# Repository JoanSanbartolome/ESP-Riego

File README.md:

# ESP-Riego

Controlador inalámbrico de riego por goteo basado en ESP32 e integrado en Home Assistant mediante ESPHome.

Este repositorio contiene el rediseño (v2) de la PCB desarrollada en el Trabajo Fin de Grado de Joan San Bartolomé Ferri. El proyecto original del TFG no se modifica: se importa como referencia y la v2 se diseña desde cero a partir de su análisis.

La v2 tiene 6 salidas de 24 V DC con *high-side* inteligente y limitador común, sensor de temperatura y humedad en placa, pulsadores y un conector de expansión por I²C.

## Estado

| Fase | Estado | Etiqueta |
|---|---|---|
| 0. Análisis, especificaciones y plan | ✅ | — |
| 1. Importación de la v1 a KiCad 10 | ✅ | `v1.1-tfg` |
| 2. Arquitectura y componentes | ✅ (falta la alternativa de U1) | — |
| 3. Esquema v2 | ✅ | `v2.0-sch` |
| 4. Layout v2 | ⏳ (prueba de colocación, SPEC-0037) | — |
| 5. Fabricación | — | — |
| 6. Firmware y validación | — | — |

El esquema tiene ERC limpio, 12 páginas y 187 piezas, y cuesta 27,46 USD por placa en un pedido de 5. Lo que toca ahora está en [`gestion/ESTADO.md`](gestion/ESTADO.md).

## Documentación

1. [Análisis de la PCB v1](docs/01-analisis-v1.md): estado de la placa del TFG y hallazgos.
2. [Especificaciones de la PCB v2](docs/02-especificaciones-v2.md): requisitos y criterios de aceptación.
3. [Plan de diseño](docs/03-plan-de-diseno.md): fases e hitos.
4. [Arquitectura](docs/diseno/arquitectura.md): bloques, presupuesto de potencia y GPIO. Cada bloque tiene su documento de cálculos y restricciones de layout en [`docs/diseno/`](docs/diseno/): alimentación, MCU, salidas, sensores y conectores.
5. [Decisiones](gestion/decisiones/): `DEC-0001` … `DEC-0016`.
6. [Sistema de gestión](gestion/README.md): roles, ciclo de vida de las specs, commits y auditoría. Estado de cada spec en el [tablero](gestion/TABLERO.md) y de cada requisito en la [trazabilidad](gestion/TRAZABILIDAD.md).
7. Salidas del esquema: [BOM preliminar](fabricacion/v2.0-sch/bom.csv) y [PDF](fabricacion/v2.0-sch/esquema.pdf).

## Organización del trabajo

El diseño lo hacen agentes de Claude Code coordinados por la sesión principal ([DEC-0001](gestion/decisiones/DEC-0001-orquestacion-de-agentes.md), [DEC-0009](gestion/decisiones/DEC-0009-orquestacion-v2.md) y [DEC-0010](gestion/decisiones/DEC-0010-agentes-en-opus.md)):

| Agente | Responsable de |
|---|---|
| Coordinador | Specs, órdenes, git, tablero y comunicación |
| `ing-diseno` | Cada bloque de principio a fin: cálculos, piezas, esquema y PCB, y las herramientas de KiCad |
| `jr-conformidad` | Tipo y stock, fichas, campos, BOM, CPL y paquetes de fabricación |
| `ing-validacion` | Revisión contra especificaciones e informes con veredicto |

Cada unidad de trabajo es una spec, con un bloque o un hito de layout. Tiene su propia rama, que se valida antes de integrarse en `main` con `herramientas/gestion.py` (`abrir`, `revisar`, `integrar`, `cerrar`).

## Estructura

```
.
├── docs/            Análisis, especificaciones, plan y diseño por bloque (docs/diseno/)
├── hardware/
│   ├── libraries/   Símbolos, huellas y modelos 3D propios (rutas ${KIPRJMOD})
│   ├── componentes/ Fichas de componentes y tablas de campos
│   ├── v1-tfg/      Proyecto del TFG migrado a KiCad 10
│   └── v2/          Nuevo diseño (proyecto esp-riego)
├── fabricacion/     Salidas de fabricación por versión
├── gestion/         Estado, specs, partes, informes, decisiones, checklists y plantillas
├── herramientas/    gestion.py, verificar.py y kicad/ (herramientas de diseño)
├── .claude/         Agentes, hooks de guarda y de auditoría, y memoria de los agentes
└── .githooks/       Validación de los mensajes de commit
```

`firmware/` (configuración ESPHome) se crea en la fase 6.

## Herramientas

- `python herramientas/verificar.py hardware/v2`: ERC, DRC, paridad esquema↔PCB y los puntos `[auto]` de las checklists, sin modificar el proyecto.
- `herramientas/kicad/`: hojas de esquema desde una descripción (`hoja.py`, `dibujo.py`), campos y stock (`campos.py`, `jlc.py`), sincronización con la PCB, restricciones y colocación. Su [README](herramientas/kicad/README.md) dice qué hace cada una.
- `python herramientas/gestion.py`: ciclo de las specs, tablero y trazabilidad.

## Requisitos

- [KiCad 10](https://www.kicad.org/), con su Python para las herramientas que usan `pcbnew`. Se buscan solas en `C:\Program Files\KiCad\10.0\bin`; para otra instalación, `KICAD_DIR`, `KICAD_CLI` y `KICAD_PYTHON`.
- Python 3 (scripts de `herramientas/` y hooks; solo biblioteca estándar).
- [ESPHome](https://esphome.io/) para el firmware.

Al clonar el repositorio, activa la validación de commits:

```bash
git config core.hooksPath .githooks
```

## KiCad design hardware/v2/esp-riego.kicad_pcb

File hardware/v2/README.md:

# v2 — ESP-Riego (esqueleto de trabajo)

Proyecto KiCad 10 `esp-riego`. Nació como copia de la v1 (`hardware/v1-tfg/`, etiqueta `v1.1-tfg`, SPEC-0013) y en SPEC-0014 se vació: se retiraron todos los circuitos de la v1 que no encajan en los requisitos v0.4 (`docs/02-especificaciones-v2.md`, DEC-0002, DEC-0003 y DEC-0004). El inventario de lo retirado está en `gestion/logs/SPEC-0014/01-ing-esquematicos.md`.

Cajetín: hoja de dibujo `../libraries/ESP-Riego.kicad_wks`, título «ESP-Riego v2», revisión 2.0-dev. `comment 1` lleva la descripción de cada hoja («Placa de control de riego» en la raíz).

## Hojas

| Hoja (`Sheetname` · archivo) | Bloque pendiente | Requisitos | Contenido actual |
|---|---|---|---|
| `Alimentacion` · `alimentacion.kicad_sch` (A3) | Entrada, protecciones, limitador común, buck, 3,3 V | ALI-01 … ALI-13 | **Bloque de la v2** (SPEC-0019): J1, F1, Q1, D1–D4, U1–U4, L1, JP1, TP1–TP5 y pasivos, según `docs/diseno/alimentacion.md`. Pines de hoja: `BUS_24V`, `VIN_SENSE`, `LIM_IMON`, `LIM_FLT`, `LIM_EN` y `VBUS` |
| `MCU` · `mcu.kicad_sch` (A3) | ESP32-S3-WROOM-1, USB-C, BOOT/RESET, UART | MCU-01 … MCU-07, FW-02 | **Bloque de la v2** (SPEC-0022): U5, U6, J2, J3, SW1, SW2, D5 y pasivos, según `docs/diseno/mcu.md`. 25 pines de hoja (Anexo C de `mcu.md`) |
| `Salidas` · `salidas.kicad_sch` (A4) y subhoja `Canal` · `canal.kicad_sch` (A4, 6 instancias) | 6 *high-side* BTT6050 con diagnóstico y sus bornes | REL-01 … REL-11 | **Bloque de la v2** (SPEC-0023, SPEC-0034; jerarquía en SPEC-0035): `Canal1`…`Canal6` con U7–U12, J4–J9, D6–D17, R26–R43, R45–R68 y C27–C44 (cada instancia conserva sus referencias); en Salidas, lo común: R44, C45 y C46. Pines de hoja: `BUS_24V`, `IN1`–`IN6`, `OUT_DEN` e `IS1`–`IS6`. Redes internas de cada canal: `/Salidas/CanalN/OUT`, `IN_HS`, `DEN_HS`, `IS_HS` y `LED_A` |
| `Sensores` · `sensores.kicad_sch` | Temperatura y humedad del aire de la caseta | AMB-01, AMB-02 | **Bloque de la v2** (SPEC-0029): U13 SHT40-AD1B (I²C 0x44) y C47, según `docs/diseno/sensores.md`. Pines de hoja: `I2C_SDA` e `I2C_SCL`, unidos a la hoja MCU (R24/R25 en MCU) |
| `Conectores` · `conectores.kicad_sch` (A3) | Conector de expansión, pulsadores manuales, reparto de bornes | EXP-02 … EXP-04, AMB-03, FAB-07, FAB-08 | **Bloque de la v2** (SPEC-0031): J10, U14–U18, SW3–SW8, R69–R79, C48–C52 y H1–H4, según `docs/diseno/conectores.md`. Pines de hoja: `I2C_SDA`, `I2C_SCL`, `BTN_INT`, `I2C_EXP_SDA`, `I2C_EXP_SCL`, `EXP_INT` y `EXP_EN` |

Cada bloque crea sus pines jerárquicos. En la raíz, `VBUS`, `VIN_SENSE`, `LIM_IMON`, `LIM_FLT` y `LIM_EN` unen MCU y Alimentacion con etiquetas locales (SPEC-0022); `I2C_SDA`/`I2C_SCL` unen MCU, Sensores (SPEC-0029) y Conectores; `BTN_INT`, `I2C_EXP_SDA`, `I2C_EXP_SCL`, `EXP_INT` y `EXP_EN` unen MCU y Conectores (SPEC-0031). Ya no queda ninguna marca de no conexión provisional en los pines de hoja. +5V, +3V3 y GND son símbolos de alimentación globales.

Estilo (KIC-06, DEC-0015): todas las hojas van con recuadros, cables y cifras junto a la pieza (SPEC-0035; `Sensores` fue la hoja piloto). La raíz conserva el estilo de SPEC-0032.

## Puente JP1 del limitador (DEC-0006)

JP1 es un puente de soldadura de `VIN_PROT` a `BUS_24V`, en paralelo con U1 (TPS26632). **Va abierto**, con U1 montado. Solo se cierra, con una gota de estaño, si U1 no se monta o falla abierto. Con U1 sano no se cierra: la corriente se lo saltaría. Serigrafía: «JP1: abierto = limitador · cerrado = sin limitador».

Con JP1 cerrado (y sin U1) se pierde (`docs/diseno/alimentacion.md` §3.13.9):

- la limitación común a 3,86–4,57 A (ALI-13): un corto en una salida lo limitan la fuente (≥ 5,14 A) y el BTT6050 (≥ 38 A); `VIN_PROT` cae y la lógica puede reiniciarse, así que **REL-08 no se cumple**;
- el corte general del bus por `LIM_EN`: el bus queda siempre alimentado;
- `LIM_FLT` e `LIM_IMON`: FLT lee alto siempre e IMON 0 V; en el firmware hay que activar la opción «sin limitador»;
- el *clamp* del bus a ≤ 35 V: el bus ve `VIN_PROT` hasta 53,3 V, dentro de los 65 V del BTT6050;
- el arranque suave del bus (dVdT).

Se mantiene REL-04: cada IN de las salidas tiene su *pull-down*, así que las salidas siguen apagadas en el reset y el flasheo. Los pads tienen conexión sólida a la zona: para cerrarlo hace falta un soldador potente o punta ancha.

## PCB

Sincronizada con el esquema, sin colocar ni rutar (SPEC-0019 y SPEC-0022; detalle en `gestion/logs/SPEC-0022/02-ing-layout.md`). Tiene 80 huellas: H1–H4 dentro del contorno, y fuera de él, agrupadas por posición, las 55 de Alimentacion (x 10–92, y 60–113 mm) y las 21 de la hoja MCU (x 10–64, y 120–198 mm). Sin pistas, vías ni zonas.

- Contorno **preliminar** de 100 × 70 mm en `Edge.Cuts` (FAB-08), de (100, 60) a (200, 130) mm; el origen auxiliar y el de la rejilla están en la esquina inferior izquierda. Un texto en `User.Comments` lo marca como preliminar hasta el *floorplan*.
- H1–H4 (`MountingHole_3.2mm_M3_Pad_Via`, anillo sin red), a 4 mm de los dos bordes de su esquina: H3 arriba a la izquierda, H1 arriba a la derecha, H4 abajo a la izquierda y H2 abajo a la derecha.
- Reglas de FAB-02 en el `.kicad_pro`: pista y separación ≥ 0,2 mm, vía 0,6/0,3 mm, cobre a borde ≥ 0,5 mm. Solo existe la clase `Default` (0,2 mm, vía 0,6/0,3). Las clases de FAB-03 y el `.kicad_dru` (KIC-04) llegan con el layout.
- `pcbplotparams/outputdirectory` vacío y sin `embedded_files`.

## Cómo se trabaja

Cada bloque llega con su propia spec. La PCB se actualiza desde el esquema en cada bloque; el layout definitivo se hace cuando el esquema esté estable.

Las librerías están en `../libraries/` (tablas con `${KIPRJMOD}/../libraries/...`). Desde SPEC-0019 las tablas del proyecto solo tienen `esp-riego` (símbolos y huellas propios de la v2); el resto son las oficiales de KiCad 10. Las librerías de la v1 siguen en `../libraries/` para `v1-tfg`, que tiene sus propias tablas (VAL-0014-01-02).

Verificación: `python herramientas/verificar.py hardware/v2`. Estado tras el paso 2 de SPEC-0022: ERC 0 (0 avisos), DRC 0 (0 avisos; 172 sin conectar porque la PCB no está rutada) y paridad 0. Las 21 huellas de la hoja MCU están fuera del contorno hasta la spec de colocación.

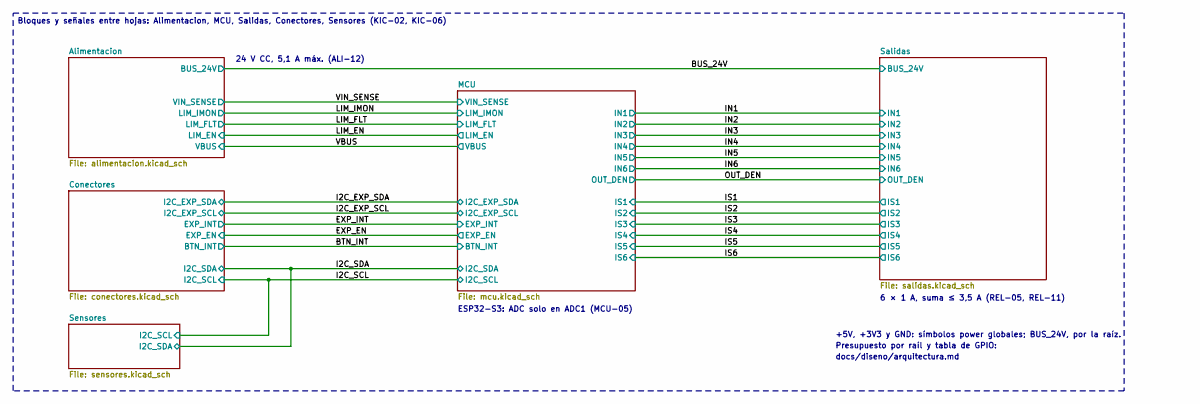
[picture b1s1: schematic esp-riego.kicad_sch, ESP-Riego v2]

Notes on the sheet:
24 V CC, 5,1 A máx. (ALI-12)
6 × 1 A, suma ≤ 3,5 A (REL-05, REL-11)
ESP32-S3: ADC solo en ADC1 (MCU-05)
+5V, +3V3 y GND: símbolos power globales; BUS_24V, por la raíz.
Presupuesto por raíl y tabla de GPIO:
docs/diseno/arquitectura.md
Bloques y señales entre hojas: Alimentacion, MCU, Salidas, Conectores, Sensores (KIC-02, KIC-06)

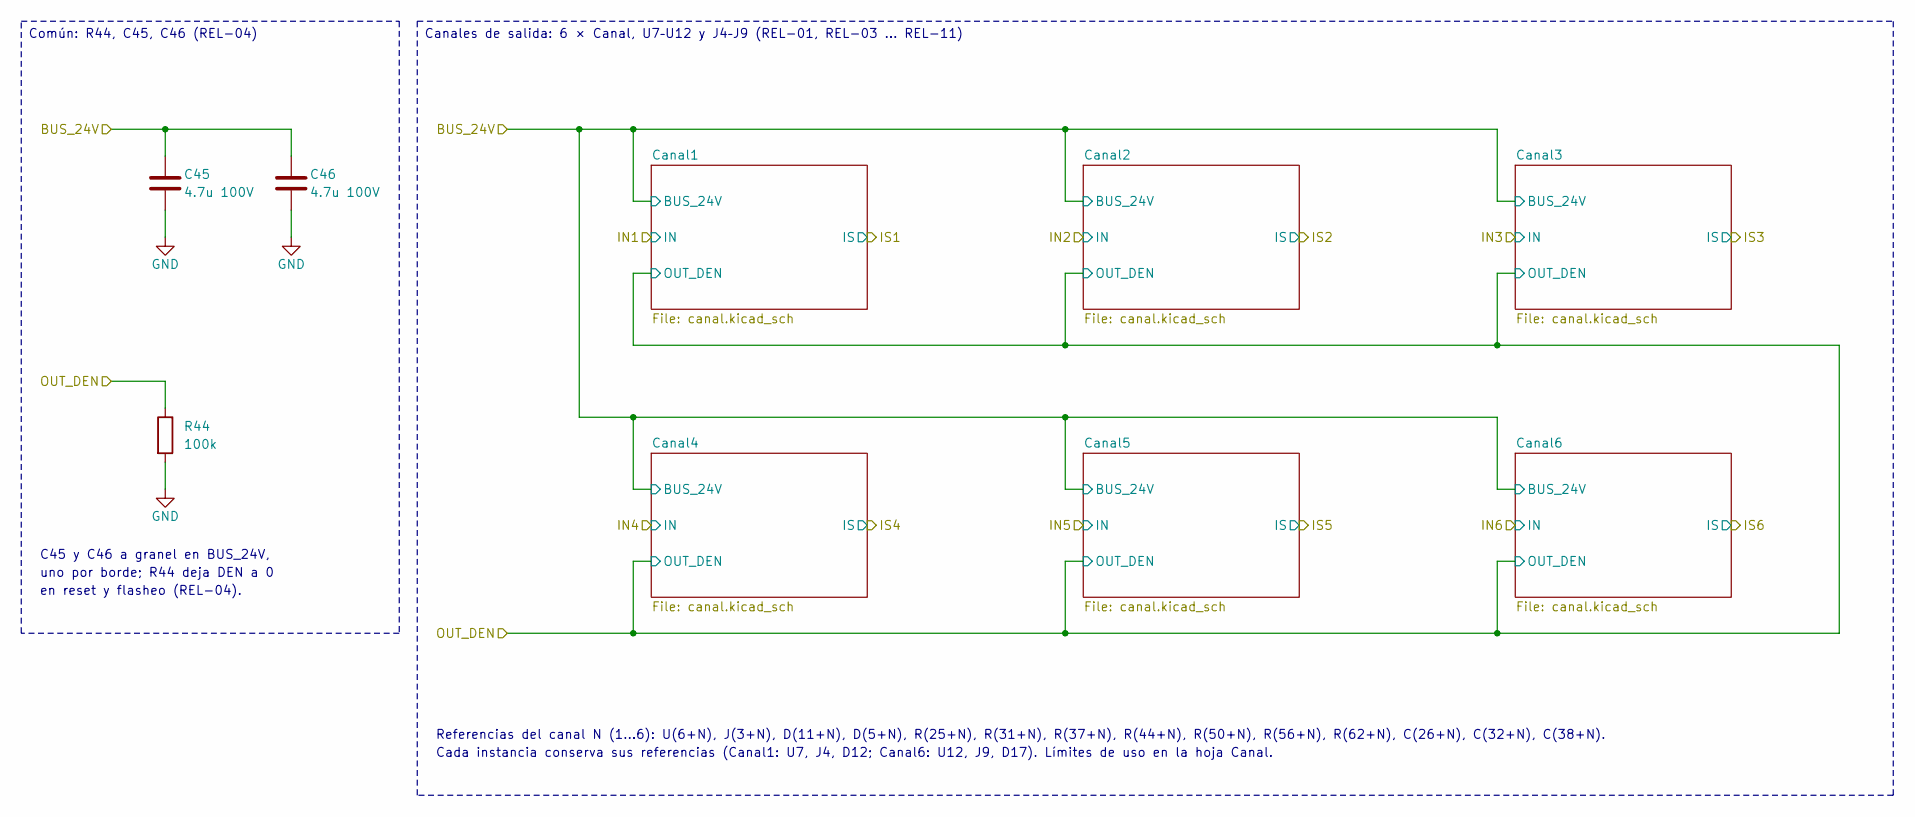
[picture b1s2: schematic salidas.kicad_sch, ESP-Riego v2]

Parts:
C45, C46: 4.7u 100V; C_1210_3225Metric; MPN FS32X475K101EGG; LCSC Part# C381466
R44: 100k; R_0603_1608Metric; MPN 0603WAF1003T5E; LCSC Part# C25803

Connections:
/BUS_24V: C45.1, C46.1; also elsewhere on the board
/OUT_DEN: R44.1; also elsewhere on the board
GND: C45.2, C46.2, R44.2; also elsewhere on the board

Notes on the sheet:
C45 y C46 a granel en BUS_24V,
uno por borde; R44 deja DEN a 0
en reset y flasheo (REL-04).
Referencias del canal N (1…6): U(6+N), J(3+N), D(11+N), D(5+N), R(25+N), R(31+N), R(37+N), R(44+N), R(50+N), R(56+N), R(62+N), C(26+N), C(32+N), C(38+N).
Cada instancia conserva sus referencias (Canal1: U7, J4, D12; Canal6: U12, J9, D17). Límites de uso en la hoja Canal.
Común: R44, C45, C46 (REL-04)
Canales de salida: 6 × Canal, U7–U12 y J4–J9 (REL-01, REL-03 … REL-11)

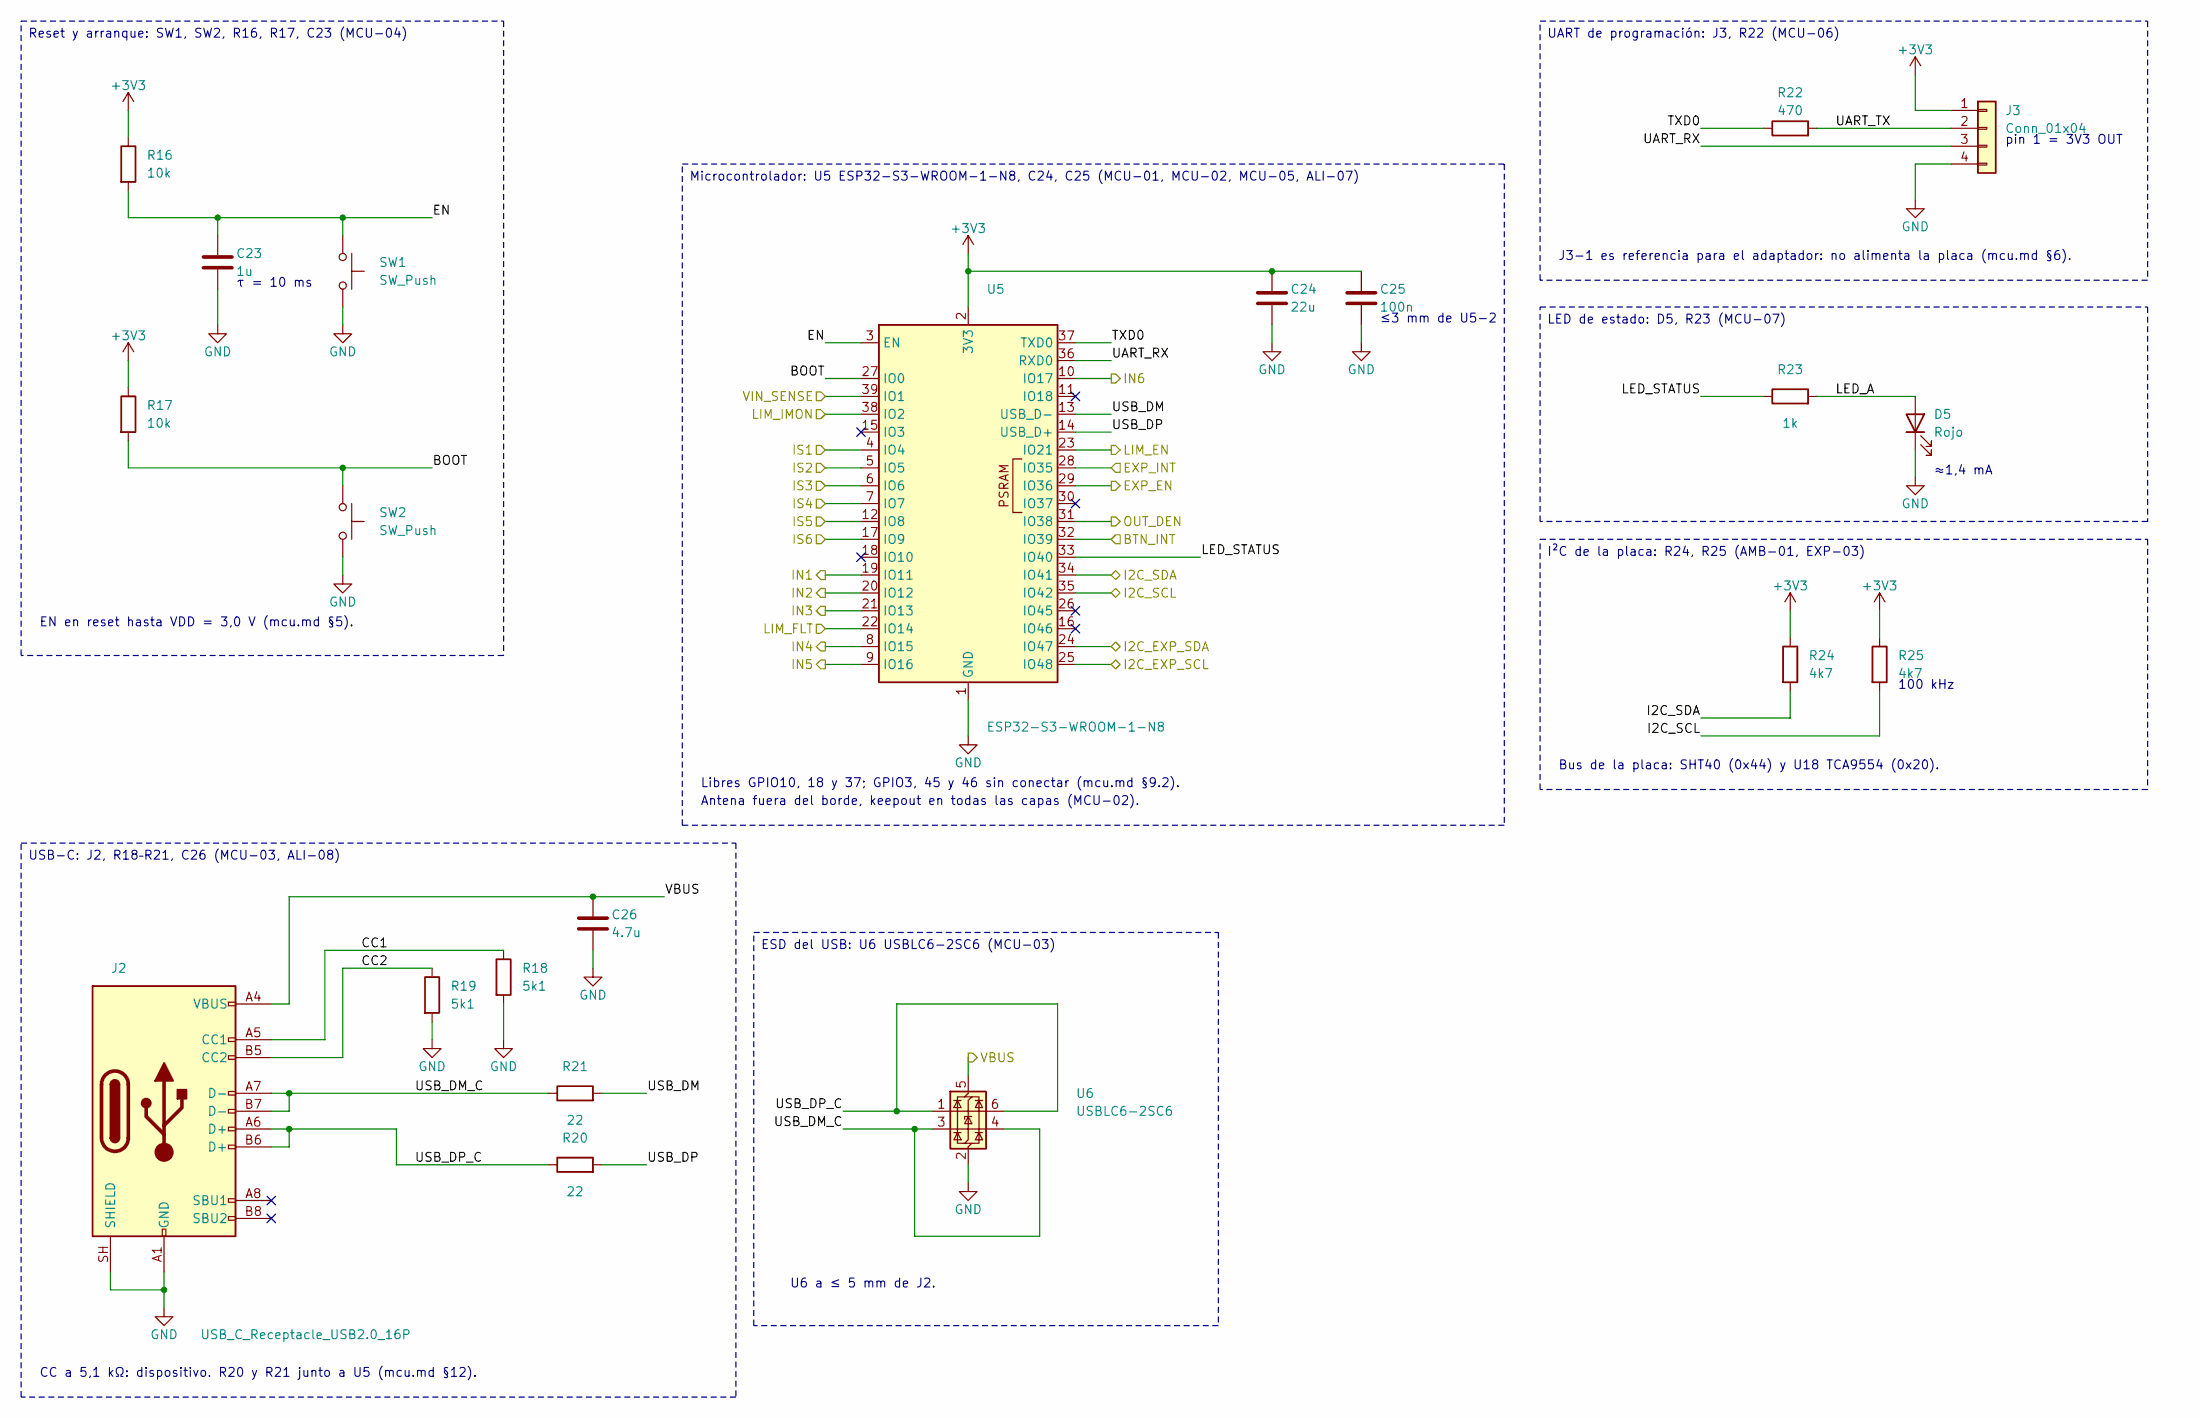
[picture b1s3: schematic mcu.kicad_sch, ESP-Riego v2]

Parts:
C23: 1u; C_0603_1608Metric; MPN CL10A105KB8NNNC; LCSC Part# C15849
C24: 22u; C_0805_2012Metric; MPN CL21A226MAQNNNE; LCSC Part# C45783
C25: 100n; C_0603_1608Metric; MPN CC0603KRX7R9BB104; LCSC Part# C14663
C26: 4.7u; C_0603_1608Metric; MPN CL10A475KO8NNNC; LCSC Part# C19666
D5: Rojo; LED_0603_1608Metric; MPN KT-0603R; LCSC Part# C2286
J2: USB_C_Receptacle_USB2.0_16P; USB_C_Receptacle_HRO_TYPE-C-31-M-12; MPN TYPE-C-31-M-12; LCSC Part# C165948
J3: Conn_01x04; PinHeader_1x04_P2.54mm_Vertical; MPN B-2100S04P-A110; LCSC Part# C124378
R16, R17: 10k; R_0603_1608Metric; MPN 0603WAF1002T5E; LCSC Part# C25804
R18, R19: 5k1; R_0603_1608Metric; MPN 0603WAF5101T5E; LCSC Part# C23186
R20, R21: 22; R_0603_1608Metric; MPN 0603WAF220JT5E; LCSC Part# C23345
R22: 470; R_0603_1608Metric; MPN 0603WAF4700T5E; LCSC Part# C23179
R23: 1k; R_0603_1608Metric; MPN 0603WAF1001T5E; LCSC Part# C21190
R24, R25: 4k7; R_0603_1608Metric; MPN 0603WAF4701T5E; LCSC Part# C23162
SW1, SW2: SW_Push; SW_Push_1P1T_XKB_TS-1187A; MPN TS-1187A-B-A-B; LCSC Part# C318884
U5: ESP32-S3-WROOM-1-N8; ESP32-S3-WROOM-1; MPN ESP32-S3-WROOM-1-N8; LCSC Part# C2913198
U6: USBLC6-2SC6; SOT-23-6; MPN USBLC6-2SC6; LCSC Part# C7519

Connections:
+3V3: C24.1, C25.1, J3.1, R16.1, R17.1, R24.1, R25.1, U5.2 (3V3); also elsewhere on the board
/BTN_INT: U5.32 (IO39); also elsewhere on the board
/EXP_EN: U5.29 (IO36); also elsewhere on the board
/EXP_INT: U5.28 (IO35); also elsewhere on the board
/I2C_EXP_SCL: U5.25 (IO48); also elsewhere on the board
/I2C_EXP_SDA: U5.24 (IO47); also elsewhere on the board
/I2C_SCL: R25.2, U5.35 (IO42); also elsewhere on the board
/I2C_SDA: R24.2, U5.34 (IO41); also elsewhere on the board
/IN1: U5.19 (IO11); also elsewhere on the board
/IN2: U5.20 (IO12); also elsewhere on the board
/IN3: U5.21 (IO13); also elsewhere on the board
/IN4: U5.8 (IO15); also elsewhere on the board
/IN5: U5.9 (IO16); also elsewhere on the board
/IN6: U5.10 (IO17); also elsewhere on the board
/IS1: U5.4 (IO4); also elsewhere on the board
/IS2: U5.5 (IO5); also elsewhere on the board
/IS3: U5.6 (IO6); also elsewhere on the board
/IS4: U5.7 (IO7); also elsewhere on the board
/IS5: U5.12 (IO8); also elsewhere on the board
/IS6: U5.17 (IO9); also elsewhere on the board
/LIM_EN: U5.23 (IO21); also elsewhere on the board
/LIM_FLT: U5.22 (IO14); also elsewhere on the board
/LIM_IMON: U5.38 (IO2); also elsewhere on the board
/MCU/BOOT: R17.2, SW2.1, U5.27 (IO0)
/MCU/CC1: J2.A5 (CC1), R18.1
/MCU/CC2: J2.B5 (CC2), R19.1
/MCU/EN: C23.1, R16.2, SW1.1, U5.3 (EN)
/MCU/LED_A: D5.2 (A), R23.2
/MCU/LED_STATUS: R23.1, U5.33 (IO40)
/MCU/TXD0: R22.1, U5.37 (TXD0)
/MCU/UART_RX: J3.3, U5.36 (RXD0)
/MCU/UART_TX: J3.2, R22.2
/MCU/USB_DM: R21.2, U5.13 (USB_D-)
/MCU/USB_DM_C: J2.A7 (D-), J2.B7 (D-), R21.1, U6.3 (I/O2), U6.4 (I/O2)
/MCU/USB_DP: R20.2, U5.14 (USB_D+)
/MCU/USB_DP_C: J2.A6 (D+), J2.B6 (D+), R20.1, U6.1 (I/O1), U6.6 (I/O1)
/OUT_DEN: U5.31 (IO38); also elsewhere on the board
/VBUS: C26.1, J2.A4 (VBUS), J2.A9 (VBUS), J2.B4 (VBUS), J2.B9 (VBUS), U6.5 (VBUS); also elsewhere on the board
/VIN_SENSE: U5.39 (IO1); also elsewhere on the board
GND: C23.2, C24.2, C25.2, C26.2, D5.1 (K), J2.A1 (GND), J2.A12 (GND), J2.B1 (GND), J2.B12 (GND), J2.SH (SHIELD), J3.4, R18.2, R19.2, SW1.2, SW2.2, U5.1 (GND), U5.40 (GND), U5.41 (GND), U6.2 (GND); also elsewhere on the board

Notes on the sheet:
τ = 10 ms
EN en reset hasta VDD = 3,0 V (mcu.md §5).
≤3 mm de U5-2
Libres GPIO10, 18 y 37; GPIO3, 45 y 46 sin conectar (mcu.md §9.2).
Antena fuera del borde, keepout en todas las capas (MCU-02).
pin 1 = 3V3 OUT
J3-1 es referencia para el adaptador: no alimenta la placa (mcu.md §6).
≈1,4 mA
100 kHz
Bus de la placa: SHT40 (0x44) y U18 TCA9554 (0x20).
CC a 5,1 kΩ: dispositivo. R20 y R21 junto a U5 (mcu.md §12).
U6 a ≤ 5 mm de J2.
Reset y arranque: SW1, SW2, R16, R17, C23 (MCU-04)
Microcontrolador: U5 ESP32-S3-WROOM-1-N8, C24, C25 (MCU-01, MCU-02, MCU-05, ALI-07)
UART de programación: J3, R22 (MCU-06)
LED de estado: D5, R23 (MCU-07)
I²C de la placa: R24, R25 (AMB-01, EXP-03)
USB-C: J2, R18–R21, C26 (MCU-03, ALI-08)
ESD del USB: U6 USBLC6-2SC6 (MCU-03)

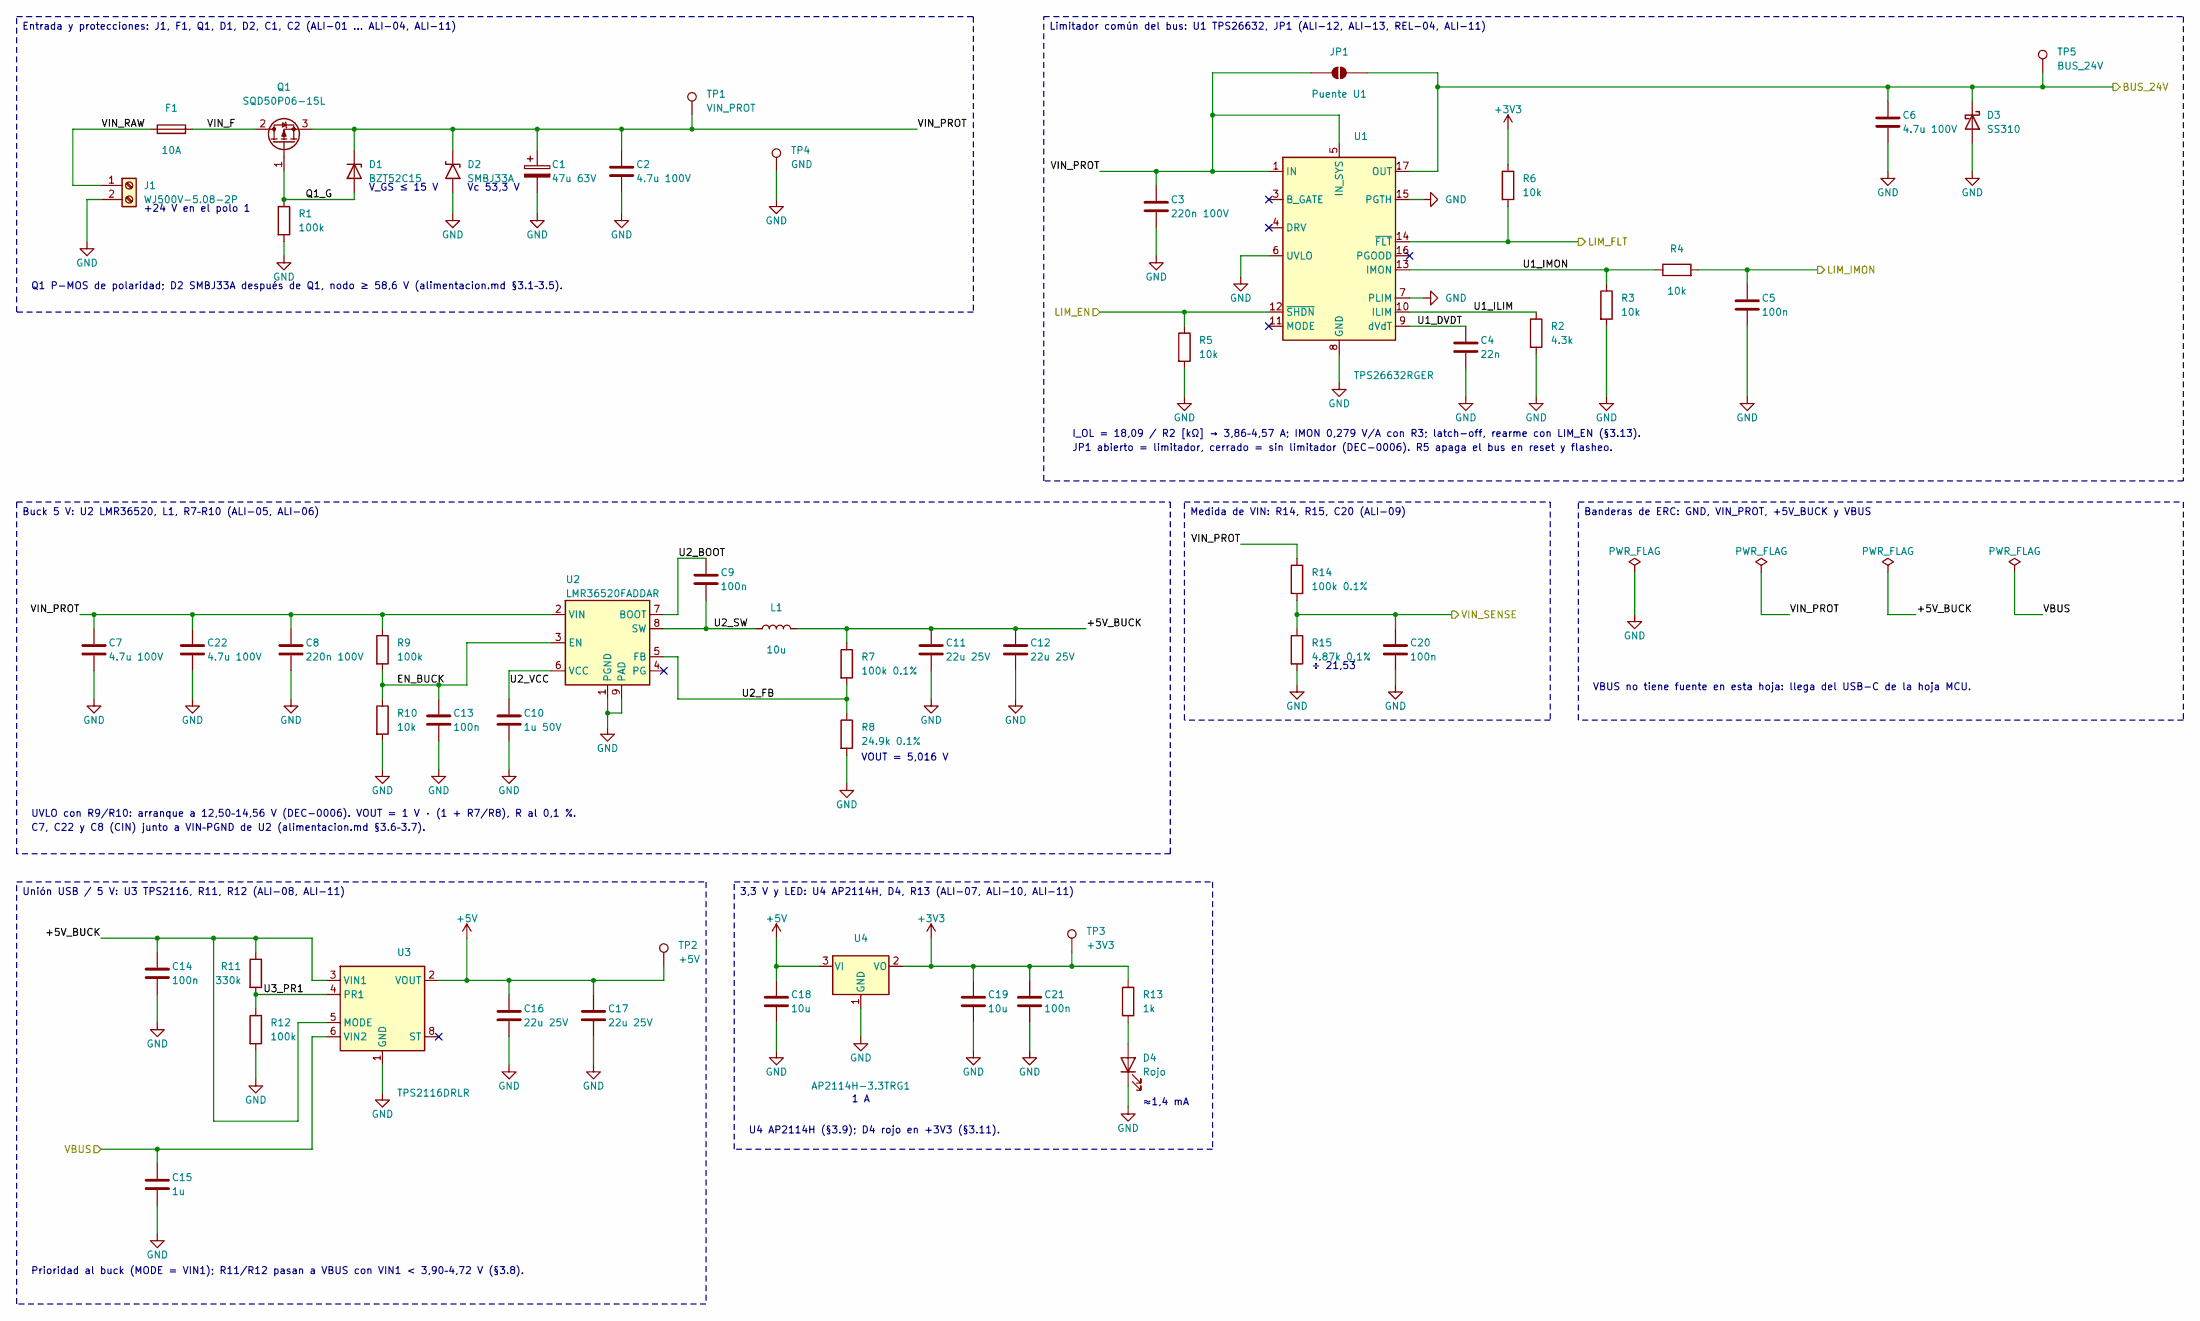
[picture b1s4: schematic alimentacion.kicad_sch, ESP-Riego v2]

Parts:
C1: 47u 63V; CP_Elec_8x10; MPN MVK 63V47 M 8*10; LCSC Part# C165628
C2, C6, C7, C22: 4.7u 100V; C_1210_3225Metric; MPN FS32X475K101EGG; LCSC Part# C381466
C3, C8: 220n 100V; C_0805_2012Metric; MPN CC0805KKX7R0BB224; LCSC Part# C513710
C4: 22n; C_0603_1608Metric; MPN CL10B223KB8NNNC; LCSC Part# C21122
C5, C9, C13, C14, C20, C21: 100n; C_0603_1608Metric; MPN CC0603KRX7R9BB104; LCSC Part# C14663
C10: 1u 50V; C_0805_2012Metric; MPN CL21B105KBFNNNE; LCSC Part# C28323
C11, C12, C16, C17: 22u 25V; C_1206_3216Metric; MPN CL31A226KAHNNNE; LCSC Part# C12891
C15: 1u; C_0603_1608Metric; MPN CL10A105KB8NNNC; LCSC Part# C15849
C18, C19: 10u; C_0603_1608Metric; MPN CL10A106KP8NNNC; LCSC Part# C19702
D1: BZT52C15; D_SOD-123; MPN BZT52C15; LCSC Part# C19077412
D2: SMBJ33A; D_SMB; MPN SMBJ33A; LCSC Part# C19077586
D3: SS310; D_SMA; MPN SS310; LCSC Part# C7420364
D4: Rojo; LED_0603_1608Metric; MPN KT-0603R; LCSC Part# C2286
F1: 10A; Fuse_Littelfuse-NANO2-451_453; MPN 0451010.MRL; LCSC Part# C44479
J1: WJ500V-5.08-2P; TerminalBlock_Kangnex_WJ500V-5.08-2P_1x02_P5.08mm_Horizontal; MPN WJ500V-5.08-2P; LCSC Part# C8465
JP1: Puente U1; SolderJumper-2_P1.8mm_Open_Pad1.2x3.0mm; MPN Sin pieza (puente de soldadura)
L1: 10u; L_Changjiang_FXL0650; MPN FXL0650-100-M; LCSC Part# C475521
Q1: SQD50P06-15L; TO-252-2; MPN SQD50P06-15L_GE3; LCSC Part# C3281500
R1, R9, R12: 100k; R_0603_1608Metric; MPN 0603WAF1003T5E; LCSC Part# C25803
R2: 4.3k; R_0603_1608Metric; MPN 0603WAF4301T5E; LCSC Part# C23159
R3, R4, R5, R6, R10: 10k; R_0603_1608Metric; MPN 0603WAF1002T5E; LCSC Part# C25804
R7, R14: 100k 0.1%; R_0603_1608Metric; MPN RT0603BRD07100KL; LCSC Part# C122538
R8: 24.9k 0.1%; R_0603_1608Metric; MPN RT0603BRD0724K9L; LCSC Part# C136967
R11: 330k; R_0603_1608Metric; MPN 0603WAF3303T5E; LCSC Part# C23137
R13: 1k; R_0603_1608Metric; MPN 0603WAF1001T5E; LCSC Part# C21190
R15: 4.87k 0.1%; R_0603_1608Metric; MPN AT0603BRD074K87L; LCSC Part# C855888
TP1: VIN_PROT; TestPoint_Pad_D2.0mm; MPN Sin pieza (pad de prueba)
TP2: +5V; TestPoint_Pad_D2.0mm; MPN Sin pieza (pad de prueba)
TP3: +3V3; TestPoint_Pad_D2.0mm; MPN Sin pieza (pad de prueba)
TP4: GND; TestPoint_THTPad_D2.0mm_Drill1.0mm; MPN Sin pieza (pad de prueba)
TP5: BUS_24V; TestPoint_Pad_D2.0mm; MPN Sin pieza (pad de prueba)
U1: TPS26632RGER; Texas_RGE0024H_VQFN-24-1EP_4x4mm_P0.5mm_EP2.7x2.7mm; MPN TPS26632RGER; LCSC Part# C1850278
U2: LMR36520FADDAR; Texas_DDA0008B_HTSOP-8-1EP_3.9x4.9mm_P1.27mm_EP2.95x4.9mm_M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; MPN LMR36520FADDAR; LCSC Part# C1858395
U3: TPS2116DRLR; SOT-583-8; MPN TPS2116DRLR; LCSC Part# C3235557
U4: AP2114H-3.3TRG1; SOT-223-3_TabPin2; MPN AP2114H-3.3TRG1; LCSC Part# C150716

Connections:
+3V3: C19.1, C21.1, R6.1, R13.1, TP3.1, U4.2 (VO); also elsewhere on the board
+5V: C16.1, C17.1, C18.1, TP2.1, U3.2 (VOUT), U3.7 (VOUT), U4.3 (VI); also elsewhere on the board
/Alimentacion/+5V_BUCK: C11.1, C12.1, C14.1, L1.2, R7.1, R11.1, U3.3 (VIN1), U3.5 (MODE)
/Alimentacion/EN_BUCK: C13.1, R9.2, R10.1, U2.3 (EN)
/Alimentacion/Q1_G: D1.2 (A), Q1.1 (G), R1.1
/Alimentacion/U1_DVDT: C4.1, U1.9 (dVdT)
/Alimentacion/U1_ILIM: R2.1, U1.10 (ILIM)
/Alimentacion/U1_IMON: R3.1, R4.1, U1.13 (IMON)
/Alimentacion/U2_BOOT: C9.1, U2.7 (BOOT)
/Alimentacion/U2_FB: R7.2, R8.1, U2.5 (FB)
/Alimentacion/U2_SW: C9.2, L1.1, U2.8 (SW)
/Alimentacion/U2_VCC: C10.1, U2.6 (VCC)
/Alimentacion/U3_PR1: R11.2, R12.1, U3.4 (PR1)
/Alimentacion/VIN_F: F1.2, Q1.2 (D)
/Alimentacion/VIN_PROT: C1.1, C2.1, C3.1, C7.1, C8.1, C22.1, D1.1 (K), D2.1 (K), JP1.1 (A), Q1.3 (S), R9.1, R14.1, TP1.1, U1.1 (IN), U1.2 (IN), U1.5 (IN_SYS), U2.2 (VIN)
/Alimentacion/VIN_RAW: F1.1, J1.1
/BUS_24V: C6.1, D3.1 (K), JP1.2 (B), TP5.1, U1.17 (OUT), U1.18 (OUT); also elsewhere on the board
/LIM_EN: R5.1, U1.12 (~SHDN); also elsewhere on the board
/LIM_FLT: R6.2, U1.14 (~FLT); also elsewhere on the board
/LIM_IMON: C5.1, R4.2; also elsewhere on the board
/VBUS: C15.1, U3.6 (VIN2); also elsewhere on the board
/VIN_SENSE: C20.1, R14.2, R15.1; also elsewhere on the board
GND: C1.2, C2.2, C3.2, C4.2, C5.2, C6.2, C7.2, C8.2, C10.2, C11.2, C12.2, C13.2, C14.2, C15.2, C16.2, C17.2, C18.2, C19.2, C20.2, C21.2, C22.2, D2.2 (A), D3.2 (A), D4.1 (K), J1.2, R1.2, R2.2, R3.2, R5.2, R8.2, R10.2, R12.2, R15.2, TP4.1, U1.6 (UVLO), U1.7 (PLIM), U1.8 (GND), U1.15 (PGTH), U1.25 (GND), U2.1 (PGND), U2.9 (PAD), U3.1 (GND), U4.1 (GND); also elsewhere on the board
unnamed: D4.2 (A), R13.2

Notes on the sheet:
+24 V en el polo 1
V_GS ≤ 15 V
Vc 53,3 V
Q1 P-MOS de polaridad; D2 SMBJ33A después de Q1, nodo ≥ 58,6 V (alimentacion.md §3.1–3.5).
I_OL = 18,09 / R2 [kΩ] → 3,86–4,57 A; IMON 0,279 V/A con R3; latch-off, rearme con LIM_EN (§3.13).
JP1 abierto = limitador, cerrado = sin limitador (DEC-0006). R5 apaga el bus en reset y flasheo.
VOUT = 5,016 V
UVLO con R9/R10: arranque a 12,50–14,56 V (DEC-0006). VOUT = 1 V · (1 + R7/R8), R al 0,1 %.
C7, C22 y C8 (CIN) junto a VIN–PGND de U2 (alimentacion.md §3.6–3.7).
Prioridad al buck (MODE = VIN1); R11/R12 pasan a VBUS con VIN1 < 3,90–4,72 V (§3.8).
1 A
≈1,4 mA
U4 AP2114H (§3.9); D4 rojo en +3V3 (§3.11).
÷ 21,53
VBUS no tiene fuente en esta hoja: llega del USB-C de la hoja MCU.
Entrada y protecciones: J1, F1, Q1, D1, D2, C1, C2 (ALI-01 … ALI-04, ALI-11)
Limitador común del bus: U1 TPS26632, JP1 (ALI-12, ALI-13, REL-04, ALI-11)
Buck 5 V: U2 LMR36520, L1, R7–R10 (ALI-05, ALI-06)
Unión USB / 5 V: U3 TPS2116, R11, R12 (ALI-08, ALI-11)
3,3 V y LED: U4 AP2114H, D4, R13 (ALI-07, ALI-10, ALI-11)
Medida de VIN: R14, R15, C20 (ALI-09)
Banderas de ERC: GND, VIN_PROT, +5V_BUCK y VBUS

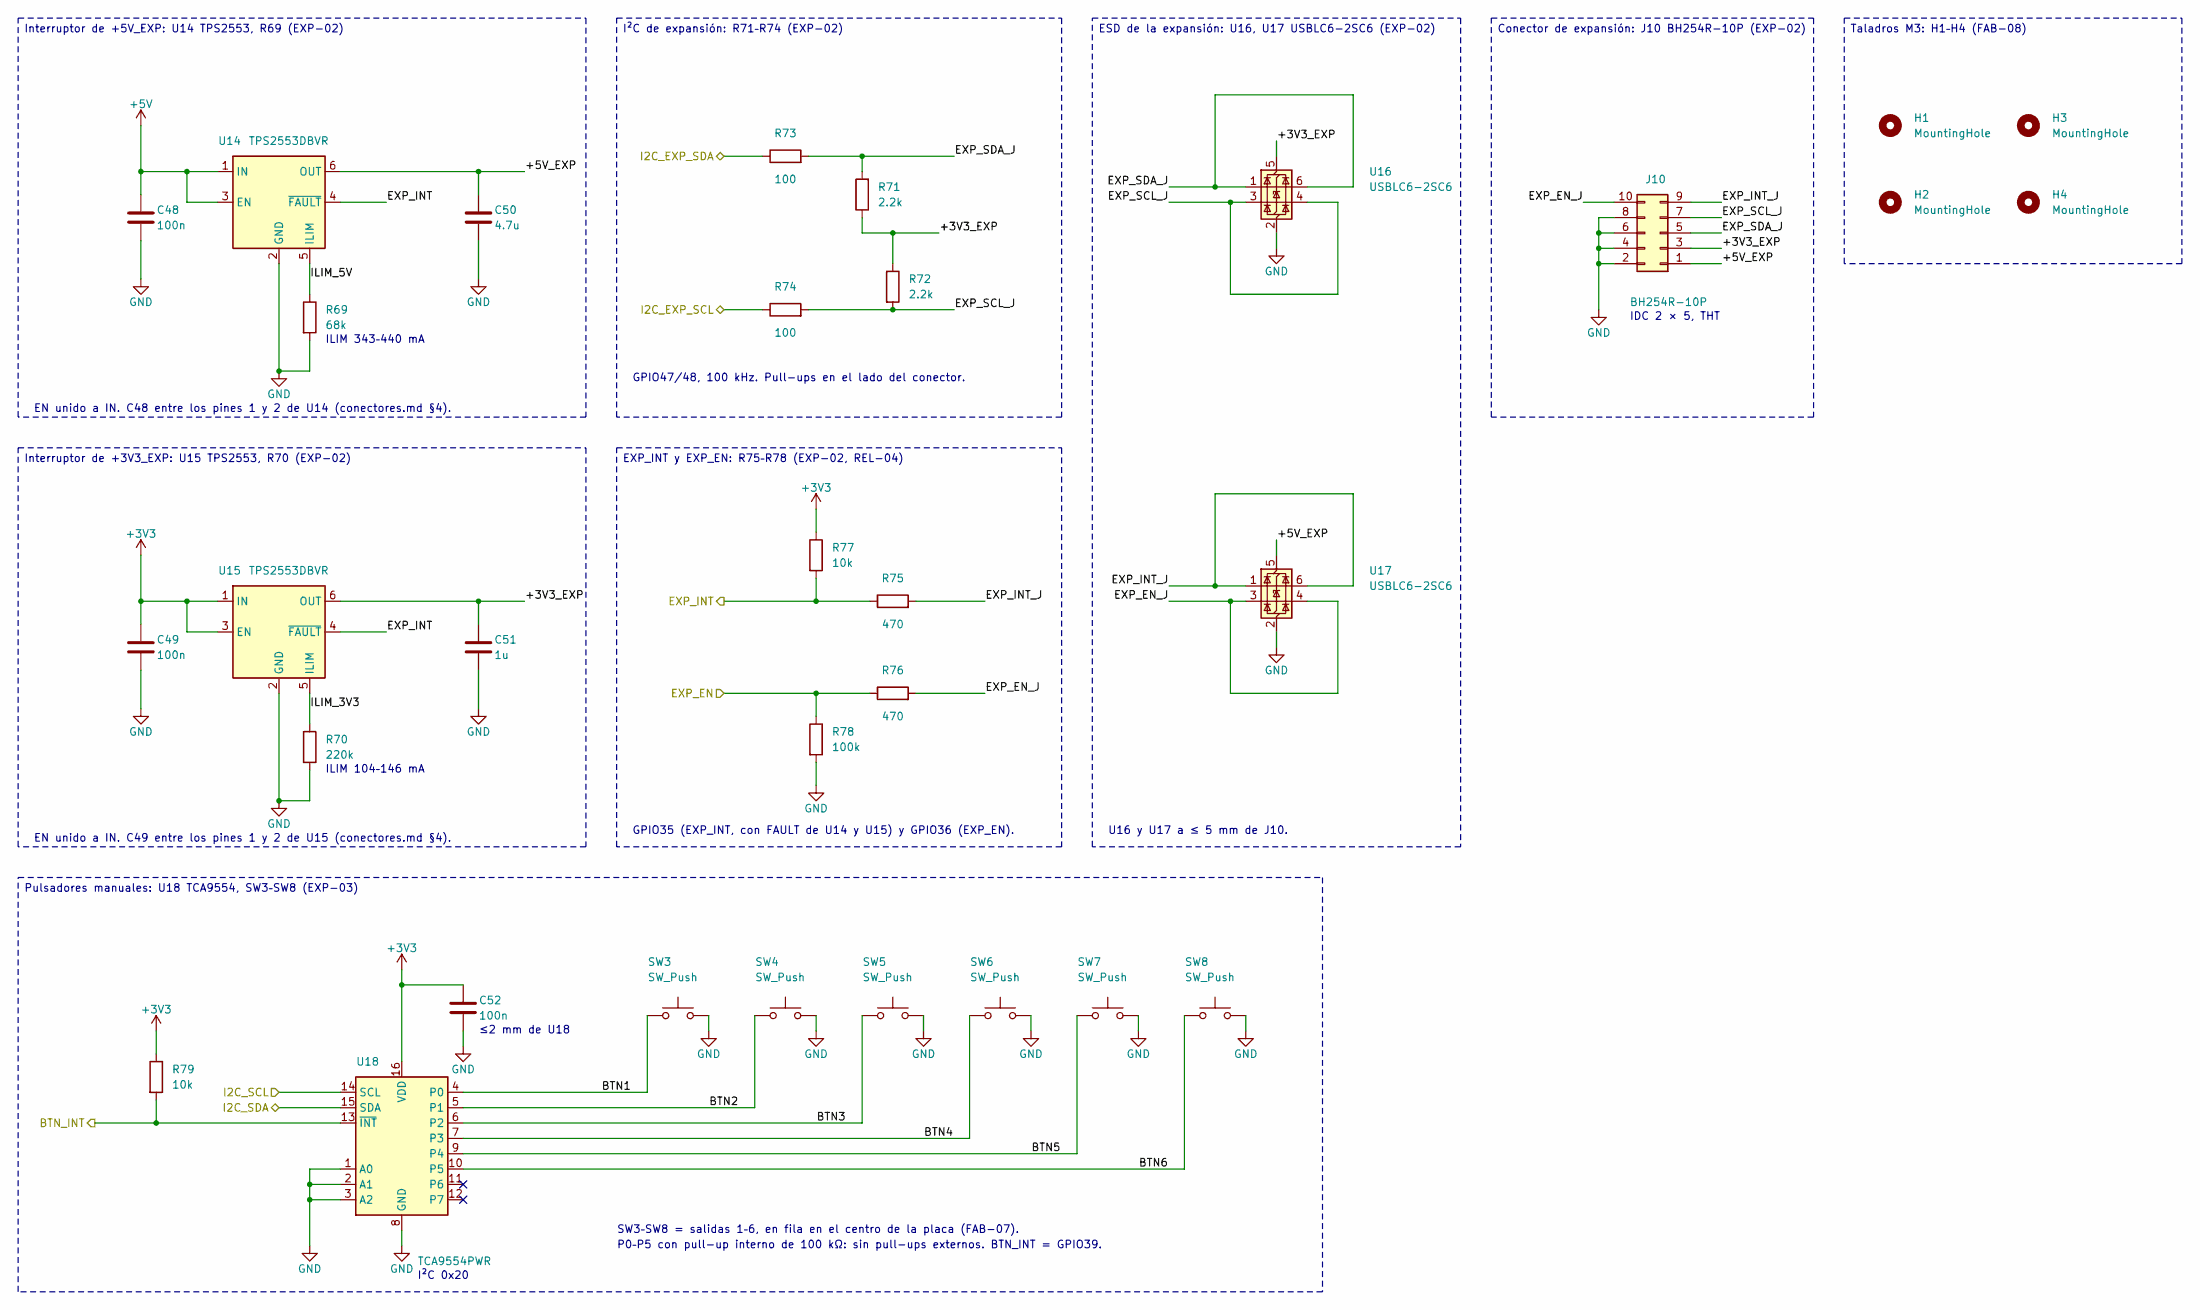
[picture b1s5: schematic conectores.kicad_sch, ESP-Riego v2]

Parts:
C48, C49, C52: 100n; C_0603_1608Metric; MPN CC0603KRX7R9BB104; LCSC Part# C14663
C50: 4.7u; C_0603_1608Metric; MPN CL10A475KO8NNNC; LCSC Part# C19666
C51: 1u; C_0603_1608Metric; MPN CL10A105KB8NNNC; LCSC Part# C15849
H1, H2, H3, H4: MountingHole; MountingHole_3.2mm_M3_Pad_Via
J10: BH254R-10P; IDC-Header_2x05_P2.54mm_Horizontal; MPN BH254R-10P; LCSC Part# C492448
R69: 68k; R_0603_1608Metric; MPN 0603WAF6802T5E; LCSC Part# C23231
R70: 220k; R_0603_1608Metric; MPN 0603WAF2203T5E; LCSC Part# C22961
R71, R72: 2.2k; R_0603_1608Metric; MPN 0603WAF2201T5E; LCSC Part# C4190
R73, R74: 100; R_0603_1608Metric; MPN 0603WAF1000T5E; LCSC Part# C22775
R75, R76: 470; R_0603_1608Metric; MPN 0603WAF4700T5E; LCSC Part# C23179
R77, R79: 10k; R_0603_1608Metric; MPN 0603WAF1002T5E; LCSC Part# C25804
R78: 100k; R_0603_1608Metric; MPN 0603WAF1003T5E; LCSC Part# C25803
SW3, SW4, SW5, SW6, SW7, SW8: SW_Push; SW_Push_1P1T_XKB_TS-1187A; MPN TS-1187A-B-A-B; LCSC Part# C318884
U14, U15: TPS2553DBVR; SOT-23-6; MPN TPS2553DBVR; LCSC Part# C55266
U16, U17: USBLC6-2SC6; SOT-23-6; MPN USBLC6-2SC6; LCSC Part# C7519
U18: TCA9554PWR; TSSOP-16_4.4x5mm_P0.65mm; MPN TCA9554PWR; LCSC Part# C477924

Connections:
+3V3: C49.1, C52.1, R77.1, R79.1, U15.1 (IN), U15.3 (EN), U18.16 (VDD); also elsewhere on the board
+5V: C48.1, U14.1 (IN), U14.3 (EN); also elsewhere on the board
/BTN_INT: R79.2, U18.13 (~INT); also elsewhere on the board
/Conectores/+3V3_EXP: C51.1, J10.3, R71.1, R72.1, U15.6 (OUT), U16.5 (VBUS)
/Conectores/+5V_EXP: C50.1, J10.1, U14.6 (OUT), U17.5 (VBUS)
/Conectores/BTN1: SW3.1, U18.4 (P0)
/Conectores/BTN2: SW4.1, U18.5 (P1)
/Conectores/BTN3: SW5.1, U18.6 (P2)
/Conectores/BTN4: SW6.1, U18.7 (P3)
/Conectores/BTN5: SW7.1, U18.9 (P4)
/Conectores/BTN6: SW8.1, U18.10 (P5)
/Conectores/EXP_EN_J: J10.10, R76.2, U17.3 (I/O2), U17.4 (I/O2)
/Conectores/EXP_INT_J: J10.9, R75.2, U17.1 (I/O1), U17.6 (I/O1)
/Conectores/EXP_SCL_J: J10.7, R72.2, R74.2, U16.3 (I/O2), U16.4 (I/O2)
/Conectores/EXP_SDA_J: J10.5, R71.2, R73.2, U16.1 (I/O1), U16.6 (I/O1)
/Conectores/ILIM_3V3: R70.1, U15.5 (ILIM)
/Conectores/ILIM_5V: R69.1, U14.5 (ILIM)
/EXP_EN: R76.1, R78.1; also elsewhere on the board
/EXP_INT: R75.1, R77.2, U14.4 (~FAULT), U15.4 (~FAULT); also elsewhere on the board
/I2C_EXP_SCL: R74.1; also elsewhere on the board
/I2C_EXP_SDA: R73.1; also elsewhere on the board
/I2C_SCL: U18.14 (SCL); also elsewhere on the board
/I2C_SDA: U18.15 (SDA); also elsewhere on the board
GND: C48.2, C49.2, C50.2, C51.2, C52.2, J10.2, J10.4, J10.6, J10.8, R69.2, R70.2, R78.2, SW3.2, SW4.2, SW5.2, SW6.2, SW7.2, SW8.2, U14.2 (GND), U15.2 (GND), U16.2 (GND), U17.2 (GND), U18.1 (A0), U18.2 (A1), U18.3 (A2), U18.8 (GND); also elsewhere on the board

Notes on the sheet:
ILIM 343–440 mA
EN unido a IN. C48 entre los pines 1 y 2 de U14 (conectores.md §4).
ILIM 104–146 mA
EN unido a IN. C49 entre los pines 1 y 2 de U15 (conectores.md §4).
GPIO47/48, 100 kHz. Pull-ups en el lado del conector.
GPIO35 (EXP_INT, con FAULT de U14 y U15) y GPIO36 (EXP_EN).
U16 y U17 a ≤ 5 mm de J10.
IDC 2 × 5, THT
I²C 0x20
≤2 mm de U18
SW3–SW8 = salidas 1–6, en fila en el centro de la placa (FAB-07).
P0–P5 con pull-up interno de 100 kΩ: sin pull-ups externos. BTN_INT = GPIO39.
Interruptor de +5V_EXP: U14 TPS2553, R69 (EXP-02)
Interruptor de +3V3_EXP: U15 TPS2553, R70 (EXP-02)
I²C de expansión: R71–R74 (EXP-02)
EXP_INT y EXP_EN: R75–R78 (EXP-02, REL-04)
ESD de la expansión: U16, U17 USBLC6-2SC6 (EXP-02)
Conector de expansión: J10 BH254R-10P (EXP-02)
Taladros M3: H1–H4 (FAB-08)
Pulsadores manuales: U18 TCA9554, SW3–SW8 (EXP-03)
